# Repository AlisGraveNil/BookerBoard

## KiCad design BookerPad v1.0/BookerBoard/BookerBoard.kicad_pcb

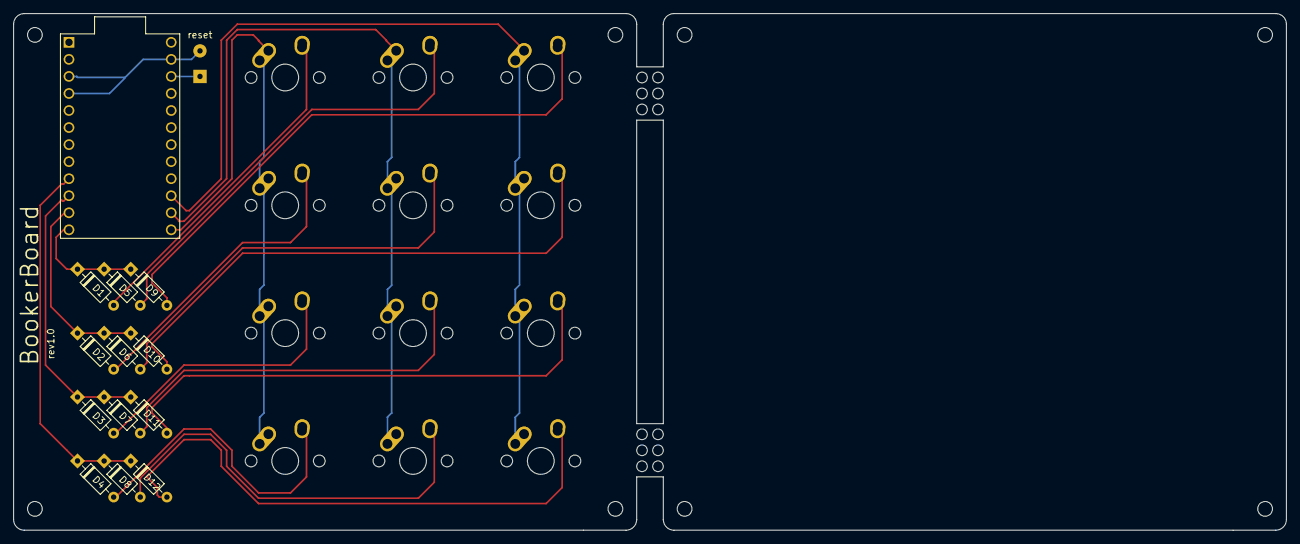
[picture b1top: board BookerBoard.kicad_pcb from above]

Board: 2 copper layers, 189.7 x 77.0 mm, 26 parts (0 on the bottom side), 21 nets.

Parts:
D1, D2, D3, D4, D5, D6, D7, D8, D9, D10, D11, D12: D_Small; D_DO-35_SOD27_P7.62mm_Horizontal
MX1, MX2, MX3, MX4, MX5, MX6, MX7, MX8, MX9, MX10, MX11, MX12: MX-NoLED; MX-1U-NoLED
U1: ProMicro
reset: Conn_02x01; SolderWirePad_1x02_P3.81mm_Drill0.8mm

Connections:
unnamed: D1.2, MX1.2
unnamed: D2.2, MX2.2
unnamed: D3.2, MX3.2
unnamed: D4.2, MX4.2
unnamed: D5.2, MX5.2
unnamed: D6.2, MX6.2
unnamed: D7.2, MX7.2
unnamed: D8.2, MX8.2
unnamed: D9.2, MX9.2
unnamed: D10.2, MX10.2
unnamed: D11.2, MX11.2
unnamed: D12.2, MX12.2
col0: MX1.1, MX2.1, MX3.1, MX4.1, U1.13
col1: MX5.1, MX6.1, MX7.1, MX8.1, U1.14
col2: MX9.1, MX10.1, MX11.1, MX12.1, U1.15
gnd: U1.3, U1.4, U1.23, reset.2
row0: D1.1, D5.1, D9.1, U1.12
row1: D2.1, D6.1, D10.1, U1.11
row2: D3.1, D7.1, D11.1, U1.10
row3: D4.1, D8.1, D12.1, U1.9
rst: U1.22, reset.1

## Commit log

2020-04-22 4/22/20 v1
2020-04-22 4/22/20 v3
2020-05-04 5/3/20 v1
